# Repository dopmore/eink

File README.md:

# Tiny-e-ink-Ebook-reader
This project aims to create a small portable e-reader, using an E-ink Display and a SD-card for storage.
It includes a Multi Directional Switch and a Select Button for inputs. While the MDS is for navigation (Next Page / Last Page), the select button is used to make a book mark and the middle button of the MDS then can be used to go back to the saved bookmark. 

I wanted to make this to be able to read books anywhere at any time without needing to carry around a big e-reader or get distracted by my phone :)!

## CAD / Assembly

The Assembly is easy as the case consists of only two parts that slide into each other and trap the PCB + Battery in between.

## PCB

The PCB will be soldered using a hotplate.

## Schematics

## PCB-order:

## Parts (LCSC):

## BOM
| Component                                | Link    / Company                                              | Price            | Shipping | 
| ---- | ---- | ---- | ---- |
| PCB + Stencil                            | jlcpcb.com | $12.44         | free (coupon) |
| PCB-Parts  | lcsc.com | $15.42 | $8.95 |
| 103450 3,7 V 1500 mAh Polymer-Lithium-Akku jst PH 2,0 mm                        | https://www.aliexpress.com/item/1005009590723370.html | $7.60 | free |
| E-paper Screen 296x128 (GDEY029T94)                | https://buy-lcd.com/products/29-inch-e-paper-screen-296x128-raspberry-pi-spi-display-gdey029t94?VariantsId=10173 | $7.91         | $10 |

Total: 62.32 (Incl. Shipping)

## Parts-Bom

| Index | LCSC#     | MPN                      | Manufacturer                 | Package                             | Customer # | Description                                                                                 | RoHS | Quantity | MOQ | Multiple | Unit Price ($) | Extended Price ($) | Product Link                                                                                             |
| ----- | --------- | ------------------------ | ---------------------------- | ----------------------------------- | ---------- | ------------------------------------------------------------------------------------------- | ---- | -------- | --- | -------- | -------------- | ------------------ | -------------------------------------------------------------------------------------------------------- |
| 1     | C325532   | RMC04022.21%N            | TyoHM                        | 0402                                |            | 2.2Ω ±1% 62.5mW 0402 Thick Film Resistor                                                    | yes  | 100      | 100 | 100      | 0.0034         | 0.34               | [https://www.lcsc.com/product-detail/C325532.html](https://www.lcsc.com/product-detail/C325532.html)     |
| 2     | C71911    | 16-213SDRC/S530-A3/TR8   | EVERLIGHT                    | 0402                                |            | Red 650nm LED Indication - Discrete 2V 0402                                                 | yes  | 20       | 20  | 20       | 0.0330         | 0.66               | [https://www.lcsc.com/product-detail/C71911.html](https://www.lcsc.com/product-detail/C71911.html)       |
| 3     | C77336    | MBR0530                  | JSCJ                         | SOD-123                             |            | Diode 30V 500mA Surface Mount SOD-123                                                       | yes  | 20       | 20  | 20       | 0.0332         | 0.66               | [https://www.lcsc.com/product-detail/C77336.html](https://www.lcsc.com/product-detail/C77336.html)       |
| 4     | C7603347  | SI1308EDL                | TECH PUBLIC                  | SOT-323                             |            | 30V 1.4A 360mW Surface Mount SOT-323                                                        | yes  | 5        | 5   | 5        | 0.0840         | 0.42               | [https://www.lcsc.com/product-detail/C7603347.html](https://www.lcsc.com/product-detail/C7603347.html)   |
| 5     | C52923    | CL05A105KA5NQNC          | Samsung Electro-Mechanics    | 0402                                |            | 1uF ±10% 25V Ceramic Capacitor X5R 0402                                                     | yes  | 100      | 100 | 100      | 0.0040         | 0.40               | [https://www.lcsc.com/product-detail/C52923.html](https://www.lcsc.com/product-detail/C52923.html)       |
| 6     | C511277   | MCP1700-3302E/TO         | MICROCHIP                    | TO-92-3                             |            | 3.3V Positive Fixed TO-92-3 Voltage Regulators - Linear, Low Drop Out (LDO) Regulators RoHS | yes  | 1        | 1   | 1        | 0.8030         | 0.80               | [https://www.lcsc.com/product-detail/C511277.html](https://www.lcsc.com/product-detail/C511277.html)     |
| 7     | C481407   | NX3225GA-12MHZ-STD-CRG-2 | NDK                          | SMD3225-4P                          |            | Crystal 12MHz ±20ppm 8pF 100Ω SMD3225-4P                                                    | yes  | 5        | 5   | 5        | 0.2377         | 1.19               | [https://www.lcsc.com/product-detail/C481407.html](https://www.lcsc.com/product-detail/C481407.html)     |
| 8     | C47647    | PH-2P                    | BOOMELE(Boom Precision Elec) | SMD,P=2mm,Surface Mount,Right Angle |            | Connector Header 2 position 2mm Pitch Surface Mount, Right Angle                            | yes  | 12       | 12  | 12       | 0.0614         | 0.74               | [https://www.lcsc.com/product-detail/C47647.html](https://www.lcsc.com/product-detail/C47647.html)       |
| 9     | C424093   | MCP73831T-2ACI/OT        | MICROCHIP                    | SOT-23-5                            |            | 3.75V~6V Lithium Battery 1 550mA SOT-23-5 Battery Chargers ICs RoHS                         | yes  | 1        | 1   | 1        | 0.7611         | 0.76               | [https://www.lcsc.com/product-detail/C424093.html](https://www.lcsc.com/product-detail/C424093.html)     |
| 10    | C4109     | 0402WGF2001TCE           | UNI-ROYAL                    | 0402                                |            | 2kΩ ±1% 62.5mW 0402 Thick Film Resistor                                                     | yes  | 100      | 100 | 100      | 0.0008         | 0.08               | [https://www.lcsc.com/product-detail/C4109.html](https://www.lcsc.com/product-detail/C4109.html)         |
| 11    | C410351   | TF-015                   | Hanbo Electronic             | SMD                                 |            | Micro SD card (TF card) Connector and Ejector Push-Push Surface Mount                       | yes  | 5        | 5   | 5        | 0.1383         | 0.69               | [https://www.lcsc.com/product-detail/C410351.html](https://www.lcsc.com/product-detail/C410351.html)     |
| 12    | C388885   | EVQPUD02K                | PANASONIC                    | SMD,4.7x4.5mm                       |            | Tactile Switch SPST 2.2N 1.65mm J-Lead 4.7mm x 4.5mm Surface Mount, Right Angle             | yes  | 5        | 5   | 5        | 0.2299         | 1.15               | [https://www.lcsc.com/product-detail/C388885.html](https://www.lcsc.com/product-detail/C388885.html)     |
| 13    | C354600   | CKCS5020-47uH/M          | CENKER                       | SMD,5x5mm                           |            | 750mA 47uH ±20% 770mA 580mΩ Magnetic Shielded Inductor SMD,5x5mm Fixed Inductors RoHS       | yes  | 10       | 10  | 10       | 0.0504         | 0.50               | [https://www.lcsc.com/product-detail/C354600.html](https://www.lcsc.com/product-detail/C354600.html)     |
| 14    | C347476   | AO3401A                  | UMW                          | SOT-23                              |            | P-Channel 30V 4.2A 1.4W Surface Mount SOT-23                                                | yes  | 20       | 20  | 20       | 0.0321         | 0.64               | [https://www.lcsc.com/product-detail/C347476.html](https://www.lcsc.com/product-detail/C347476.html)     |
| 15    | C11702    | 0402WGF1001TCE           | UNI-ROYAL                    | 0402                                |            | 1kΩ ±1% 62.5mW 0402 Thick Film Resistor                                                     | yes  | 100      | 100 | 100      | 0.0011         | 0.11               | [https://www.lcsc.com/product-detail/C11702.html](https://www.lcsc.com/product-detail/C11702.html)       |
| 16    | C318954   | TM-2011                  | XKB Connection               | SMD-5P,19.7x14.8mm                  |            | SMD-5P,19.7x14.8mm Navigation Switches, Joystick RoHS                                       | yes  | 5        | 5   | 5        | 0.2672         | 1.34               | [https://www.lcsc.com/product-detail/C318954.html](https://www.lcsc.com/product-detail/C318954.html)     |
| 17    | C25905    | 0402WGF5101TCE           | UNI-ROYAL                    | 0402                                |            | 5.1kΩ ±1% 62.5mW 0402 Thick Film Resistor                                                   | yes  | 100      | 100 | 100      | 0.0009         | 0.09               | [https://www.lcsc.com/product-detail/C25905.html](https://www.lcsc.com/product-detail/C25905.html)       |
| 18    | C25744    | 0402WGF1002TCE           | UNI-ROYAL                    | 0402                                |            | 10kΩ ±1% 62.5mW 0402 Thick Film Resistor                                                    | yes  | 100      | 100 | 100      | 0.0013         | 0.13               | [https://www.lcsc.com/product-detail/C25744.html](https://www.lcsc.com/product-detail/C25744.html)       |
| 19    | C25100    | 0402WGF270JTCE           | UNI-ROYAL                    | 0402                                |            | 27Ω ±1% 62.5mW 0402 Thick Film Resistor                                                     | yes  | 100      | 100 | 100      | 0.0008         | 0.08               | [https://www.lcsc.com/product-detail/C25100.html](https://www.lcsc.com/product-detail/C25100.html)       |
| 20    | C2456208  | W25Q16JVZPIQ TR          | Winbond                      | WSON-8-EP(5x6)                      |            | 2.7V~3.6V 16Mbit 133MHz SPI WSON-8-EP(5x6) Memory (ICs) RoHS                                | yes  | 1        | 1   | 1        | 1.2904         | 1.29               | [https://www.lcsc.com/product-detail/C2456208.html](https://www.lcsc.com/product-detail/C2456208.html)   |
| 21    | C23733    | CL05A475MP5NRNC          | Samsung Electro-Mechanics    | 0402                                |            | 4.7uF ±20% 10V Ceramic Capacitor X5R 0402                                                   | yes  | 50       | 50  | 50       | 0.0059         | 0.30               | [https://www.lcsc.com/product-detail/C23733.html](https://www.lcsc.com/product-detail/C23733.html)       |
| 22    | C2040     | RP2040                   | Raspberry Pi                 | LQFN-56(7x7)                        |            | 133MHz 30 LQFN-56(7x7) Microcontrollers RoHS                                                | yes  | 1        | 1   | 1        | 0.9482         | 0.95               | [https://www.lcsc.com/product-detail/C2040.html](https://www.lcsc.com/product-detail/C2040.html)         |
| 23    | C19702    | CL10A106KP8NNNC          | Samsung Electro-Mechanics    | 0603                                |            | 10uF ±10% 10V Ceramic Capacitor X5R 0603                                                    | yes  | 50       | 50  | 50       | 0.0080         | 0.40               | [https://www.lcsc.com/product-detail/C19702.html](https://www.lcsc.com/product-detail/C19702.html)       |
| 24    | C19077718 | FPC-0.5FX-24PH20         | Yuandi                       | SMD,P=0.5mm                         |            | FFC/FPC Connector 24 Position 0.5mm Pitch Bottom Contact                                    | yes  | 5        | 5   | 5        | 0.0927         | 0.46               | [https://www.lcsc.com/product-detail/C19077718.html](https://www.lcsc.com/product-detail/C19077718.html) |
| 25    | C165948   | TYPE-C-31-M-12           | Korean Hroparts Elec         | SMD                                 |            | USB-C (USB TYPE-C) Receptacle Connector 16 Position Surface Mount                           | yes  | 5        | 5   | 5        | 0.1701         | 0.85               | [https://www.lcsc.com/product-detail/C165948.html](https://www.lcsc.com/product-detail/C165948.html)     |
| 26    | C1562     | 0402CG330J500NT          | FH                           | 0402                                |            | 33pF ±5% 50V Ceramic Capacitor C0G 0402                                                     | yes  | 100      | 100 | 100      | 0.0013         | 0.13               | [https://www.lcsc.com/product-detail/C1562.html](https://www.lcsc.com/product-detail/C1562.html)         |
| 27    | C1525     | CL05B104KO5NNNC          | Samsung Electro-Mechanics    | 0402                                |            | 100nF ±10% 16V Ceramic Capacitor X7R 0402                                                   | yes  | 100      | 100 | 100      | 0.0013         | 0.13               | [https://www.lcsc.com/product-detail/C1525.html](https://www.lcsc.com/product-detail/C1525.html)         |

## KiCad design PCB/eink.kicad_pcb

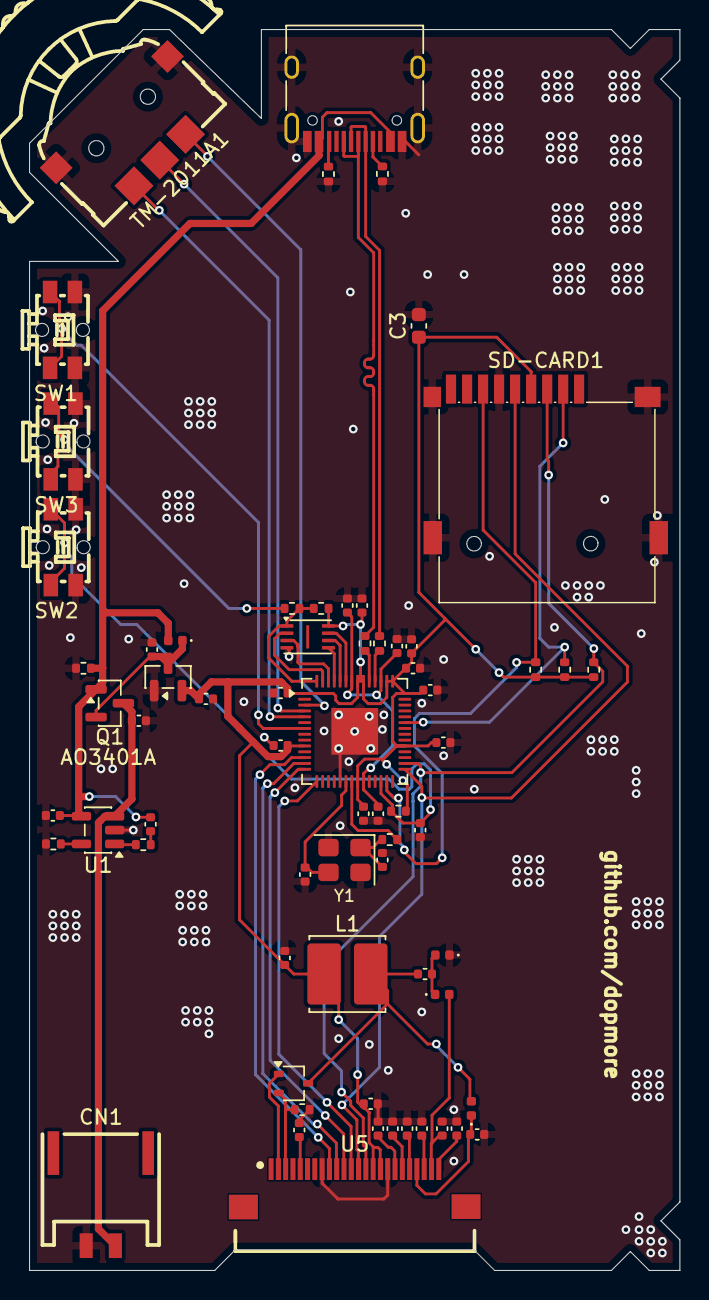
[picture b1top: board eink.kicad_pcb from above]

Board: 2 copper layers, 44.6 x 85.1 mm, 66 parts (0 on the bottom side), 50 nets.

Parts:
C1, C2, C20, C21: 4.7uF; C_0402_1005Metric
C3: 10uF; C_0603_1608Metric
C4, C6, C7, C10, C22, C23, C24, C25, C26, C27, C28, C29, C30: 1uF; C_0402_1005Metric
C5, C8, C9, C11, C12, C15, C16, C17, C18, C19: 0.1uF; C_0402_1005Metric
C13, C14: 33pF; C_0402_1005Metric
CN1: Battery; CONN-SMD_2P-P2.00_PH2.0-SPWB
D1: LED; C_0402_1005Metric
D2, D3, D4, D5: MBR0530; D_0402_1005Metric
J1: USB_C_Receptacle_USB2.0_14P; USB_C_Receptacle_HRO_TYPE-C-31-M-12
L1: 47uH; L_Cenker_CKCS5020
Q1: AO3401A; SOT-23
Q2: Si1308EDL; SOT-323_SC-70
R1, R2: 5.1K; R_0402_1005Metric
R3, R4, R5, R8, R11, R13: 10K; R_0402_1005Metric
R6, R12, R14: 1K; R_0402_1005Metric
R7: 2k; R_0402_1005Metric
R9, R10: 27; R_0402_1005Metric
R15: 2.2; R_0402_1005Metric
SD-CARD1: TF-SMD_TF-015
SW1, SW2, SW3: SW-SMD_EVQPUD02K-1
TM-2011A1: Multi-Directional Switch; SW-SMD_TM-2011
U1: MCP73831-2-OT; SOT-23-5
U2: MCP1700x-300xxTT; SOT-23
U3: RP2040; QFN-56-1EP_7x7mm_P0.4mm_EP3.2x3.2mm
U4: W25Q16JVZPIQ TR; Winbond_USON-8-1EP_3x2mm_P0.5mm_EP0.2x1.6mm
U5: FPC-SMD_24P-P0.50_YUANDI_FPC-0.5FX-24PH20
Y1: 12 MHz; Crystal_SMD_3225-4Pin_3.2x2.5mm

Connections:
+1V1: C6.1, C8.1, C9.1, U3.23 (DVDD), U3.45 (VREG_VOUT), U3.50 (DVDD)
+3.3V: C3.1, C7.1, C10.1, C11.1, C12.1, C15.1, C16.1, C17.1, C18.1, C19.1, C20.1, C23.1, L1.1, R3.1, R4.1, R5.1, R11.1, R13.1, SD-CARD1.4 (VDD), U2.2 (VO), U3.1 (IOVDD), U3.10 (IOVDD), U3.22 (IOVDD), U3.33 (IOVDD), U3.42 (IOVDD), U3.43 (ADC_AVDD), U3.44 (VREG_IN), U3.48 (USB_VDD), U3.49 (IOVDD), U4.8 (VCC), U5.15 (VDDIO), U5.16 (VCI)
/D/C: U3.14 (GPIO11), U5.11 (D/C)
/Eink BUSY: U3.12 (GPIO9), U5.9 (BUSY)
/Eink CS: U3.15 (GPIO12), U5.12 (CS)
/Eink RST: U3.13 (GPIO10), U5.10 (RES)
/GDR: Q2.1 (G), U5.2 (GDR)
/PREVGH: C22.1, D5.1 (K), U5.21 (VGH)
/PREVGL: C28.1, D3.2 (A), U5.23 (VGL)
/RESE: Q2.2 (S), R15.1, U5.3 (RESE)
GND: C1.2, C2.2, C3.2, C4.2, C5.1, C6.2, C7.2, C8.2, C9.2, C10.2, C11.2, C12.2, C13.1, C14.1, C15.2, C16.2, C17.2, C18.2, C19.2, C20.2, C22.2, C23.2, C24.2, C25.2, C26.2, C27.2, C28.2, C29.2, C30.2, CN1.2, D4.1 (K), J1.A1 (GND), J1.A12 (GND), J1.B1 (GND), J1.B12 (GND), J1.S1 (SHIELD), R1.1, R2.1, R7.2, R8.2, R15.2, SD-CARD1.6 (VSS), SD-CARD1.10 (GND), SD-CARD1.11 (GND), SD-CARD1.12 (GND), SD-CARD1.13 (GND), SW1.1, SW1.3, SW2.1, SW2.3, SW3.1, SW3.3, TM-2011A1.a, TM-2011A1.e, U1.2 (V_{SS}), U2.1 (GND), U3.19 (TESTEN), U3.57 (GND), U4.4 (GND), U5.8 (BS), U5.17 (VSS), Y1.2, Y1.4
GPIO1: TM-2011A1.b, U3.3 (GPIO1)
GPIO2: TM-2011A1.c, U3.4 (GPIO2)
GPIO3: TM-2011A1.d, U3.5 (GPIO3)
GPIO5: SW1.2, SW1.4, U3.7 (GPIO5)
GPIO16: R3.2, SD-CARD1.7 (DAT0(D0)), U3.27 (GPIO16)
GPIO18: SD-CARD1.5 (CLK(SCLK)), U3.29 (GPIO18), U5.13 (SCLK)
GPIO19: R5.2, SD-CARD1.3 (CMD(DI)), U3.30 (GPIO19), U5.14 (SDI)
GPIO25: R4.2, SD-CARD1.2 (CDDAT3(CS)), U3.37 (GPIO25)
unnamed: C14.2, R14.1, Y1.1
unnamed: D1.1 (K), R6.1
unnamed: C4.1, D2.1 (K), Q1.2 (S), U2.3 (VI)
unnamed: C21.1, D3.1 (K), D4.2 (A)
unnamed: C21.2, D5.2 (A), L1.2, Q2.3 (D)
unnamed: J1.A5 (CC1), R1.2
unnamed: J1.B5 (CC2), R2.2
unnamed: C2.1, CN1.1, Q1.3 (D), U1.3 (V_{BAT})
unnamed: R12.2, SW3.2, SW3.4
unnamed: R7.1, U1.5 (PROG)
unnamed: R6.2, U1.1 (STAT)
unnamed: C5.2, R11.2, SW2.2, SW2.4, U3.26 (RUN)
unnamed: R10.2, U3.46 (USB_DM)
unnamed: R9.2, U3.47 (USB_DP)
unnamed: C30.1, U5.24 (VCOM)
unnamed: C24.1, U5.18 (VDD)
unnamed: C25.1, U5.19 (VPP)
unnamed: C26.1, U5.20 (VSH1)
unnamed: C29.1, U5.5 (VSH2)
unnamed: C27.1, U5.22 (VSL)
QSPI_SCLK: U3.52 (QSPI_SCLK), U4.6 (CLK)
QSPI_SD0: U3.53 (QSPI_SD0), U4.5 (DI/IO_{0})
QSPI_SD1: U3.55 (QSPI_SD1), U4.2 (DO/IO_{1})
QSPI_SD2: U3.54 (QSPI_SD2), U4.3 (~WP/IO_{2})
QSPI_SD3: U3.51 (QSPI_SD3), U4.7 (~HOLD/~RESET/IO_{3})
QSP_SS: R12.1, R13.2, U3.56 (QSPI_SS), U4.1 (~CS)
USB_D+: J1.A6 (D+), J1.B6 (D+), R9.1
USB_D-: J1.A7 (D-), J1.B7 (D-), R10.1
VBUS: C1.1, D1.2 (A), D2.2 (A), J1.A4 (VBUS), J1.A9 (VBUS), J1.B4 (VBUS), J1.B9 (VBUS), Q1.1 (G), R8.1, U1.4 (V_{DD})
XIN: C13.2, U3.20 (XIN), Y1.3
XOUT: R14.2, U3.21 (XOUT)

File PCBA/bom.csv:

Designator,Footprint,Quantity,Value,LCSC Part #
"C1, C2, C20, C21",0402,4,4.7uF,
"C10, C22, C23, C24, C25, C26, C27, C28, C29, C30, C4, C6, C7",0402,13,1uF,
"C11, C12, C15, C16, C17, C18, C19, C5, C8, C9",0402,10,0.1uF,
"C13, C14",0402,2,33pF,
C3,0603,1,10uF,
CN1,CONN-SMD_2P-P2.00_PH2.0-SPWB,1,Battery,
D1,0402,1,LED,
"D2, D3, D4, D5",0402,4,MBR0530,
J1,USB_C_Receptacle_HRO_TYPE-C-31-M-12,1,USB_C_Receptacle_USB2.0_14P,
L1,L_6.3x6.3_H3,1,47uH,
Q1,SOT-23,1,AO3401A,
Q2,SOT-323_SC-70,1,Si1308EDL,
"R1, R2",0402,2,5.1K,
"R10, R9",0402,2,27,
"R11, R13, R3, R4, R5, R8",0402,6,10K,
"R12, R14, R6",0402,3,1K,
R15,0402,1,2.2,
R7,0402,1,2k,
SD-CARD1,TF-SMD_TF-015,1,~,
"SW1, SW2, SW3",SW-SMD_EVQPUD02K-1,3,~,
TM-2011A1,SW-SMD_TM-2011,1,Multi-Directional Switch,
U1,SOT-23-5,1,MCP73831-2-OT,
U2,SOT-23,1,MCP1700x-300xxTT,
U3,QFN-56-1EP_7x7mm_P0.4mm_EP3.2x3.2mm,1,RP2040,
U4,Winbond_USON-8-1EP_3x2mm_P0.5mm_EP0.2x1.6mm,1,W25Q16JVZPIQ TR,
U5,FPC-SMD_24P-P0.50_YUANDI_FPC-0.5FX-24PH20,1,~,
Y1,Crystal_SMD_3225-4Pin_3.2x2.5mm,1,12 MHz,

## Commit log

2026-04-02 Added Gerbers
2026-04-02 Add BOM and pos
2026-04-02 add firmware
2026-04-02 Enhance README with project details and visuals
    Expanded project description and added sections for CAD, PCB, and Schematics with images.
2026-05-03 Add additional images to README.md
2026-05-04 Add image to README for Tiny e-reader project
    Added an image to the README for visual reference.
2026-05-04 Add PCBA section and image to README
    Added PCBA section with image to README.
2026-05-05 Revise PCB section and add BOM details
    Updated PCB section and added BOM table with components and prices.
2026-05-05 Add BOM.csv with component details and pricing
2026-05-05 Update total cost in BOM section
    Updated total cost in BOM section to reflect new prices.
2026-05-05 Add new entries to BOM.csv
2026-05-05 Modify shipping details for PCB and Stencil
    Updated shipping information for PCB and Stencil in BOM.
2026-05-05 Enhance README with assembly and PCB information
    Added details about assembly and PCB soldering process.
2026-05-10 Add parts BOM section to README
    Added a detailed parts bill of materials (BOM) section with specifications, quantities, and links for various components.
2026-05-10 Add header and update BOM.csv entries
    Added header row and updated BOM entries.
2026-05-10 Change image source for Tiny e-reader
    Updated image source in README for Tiny e-reader.
